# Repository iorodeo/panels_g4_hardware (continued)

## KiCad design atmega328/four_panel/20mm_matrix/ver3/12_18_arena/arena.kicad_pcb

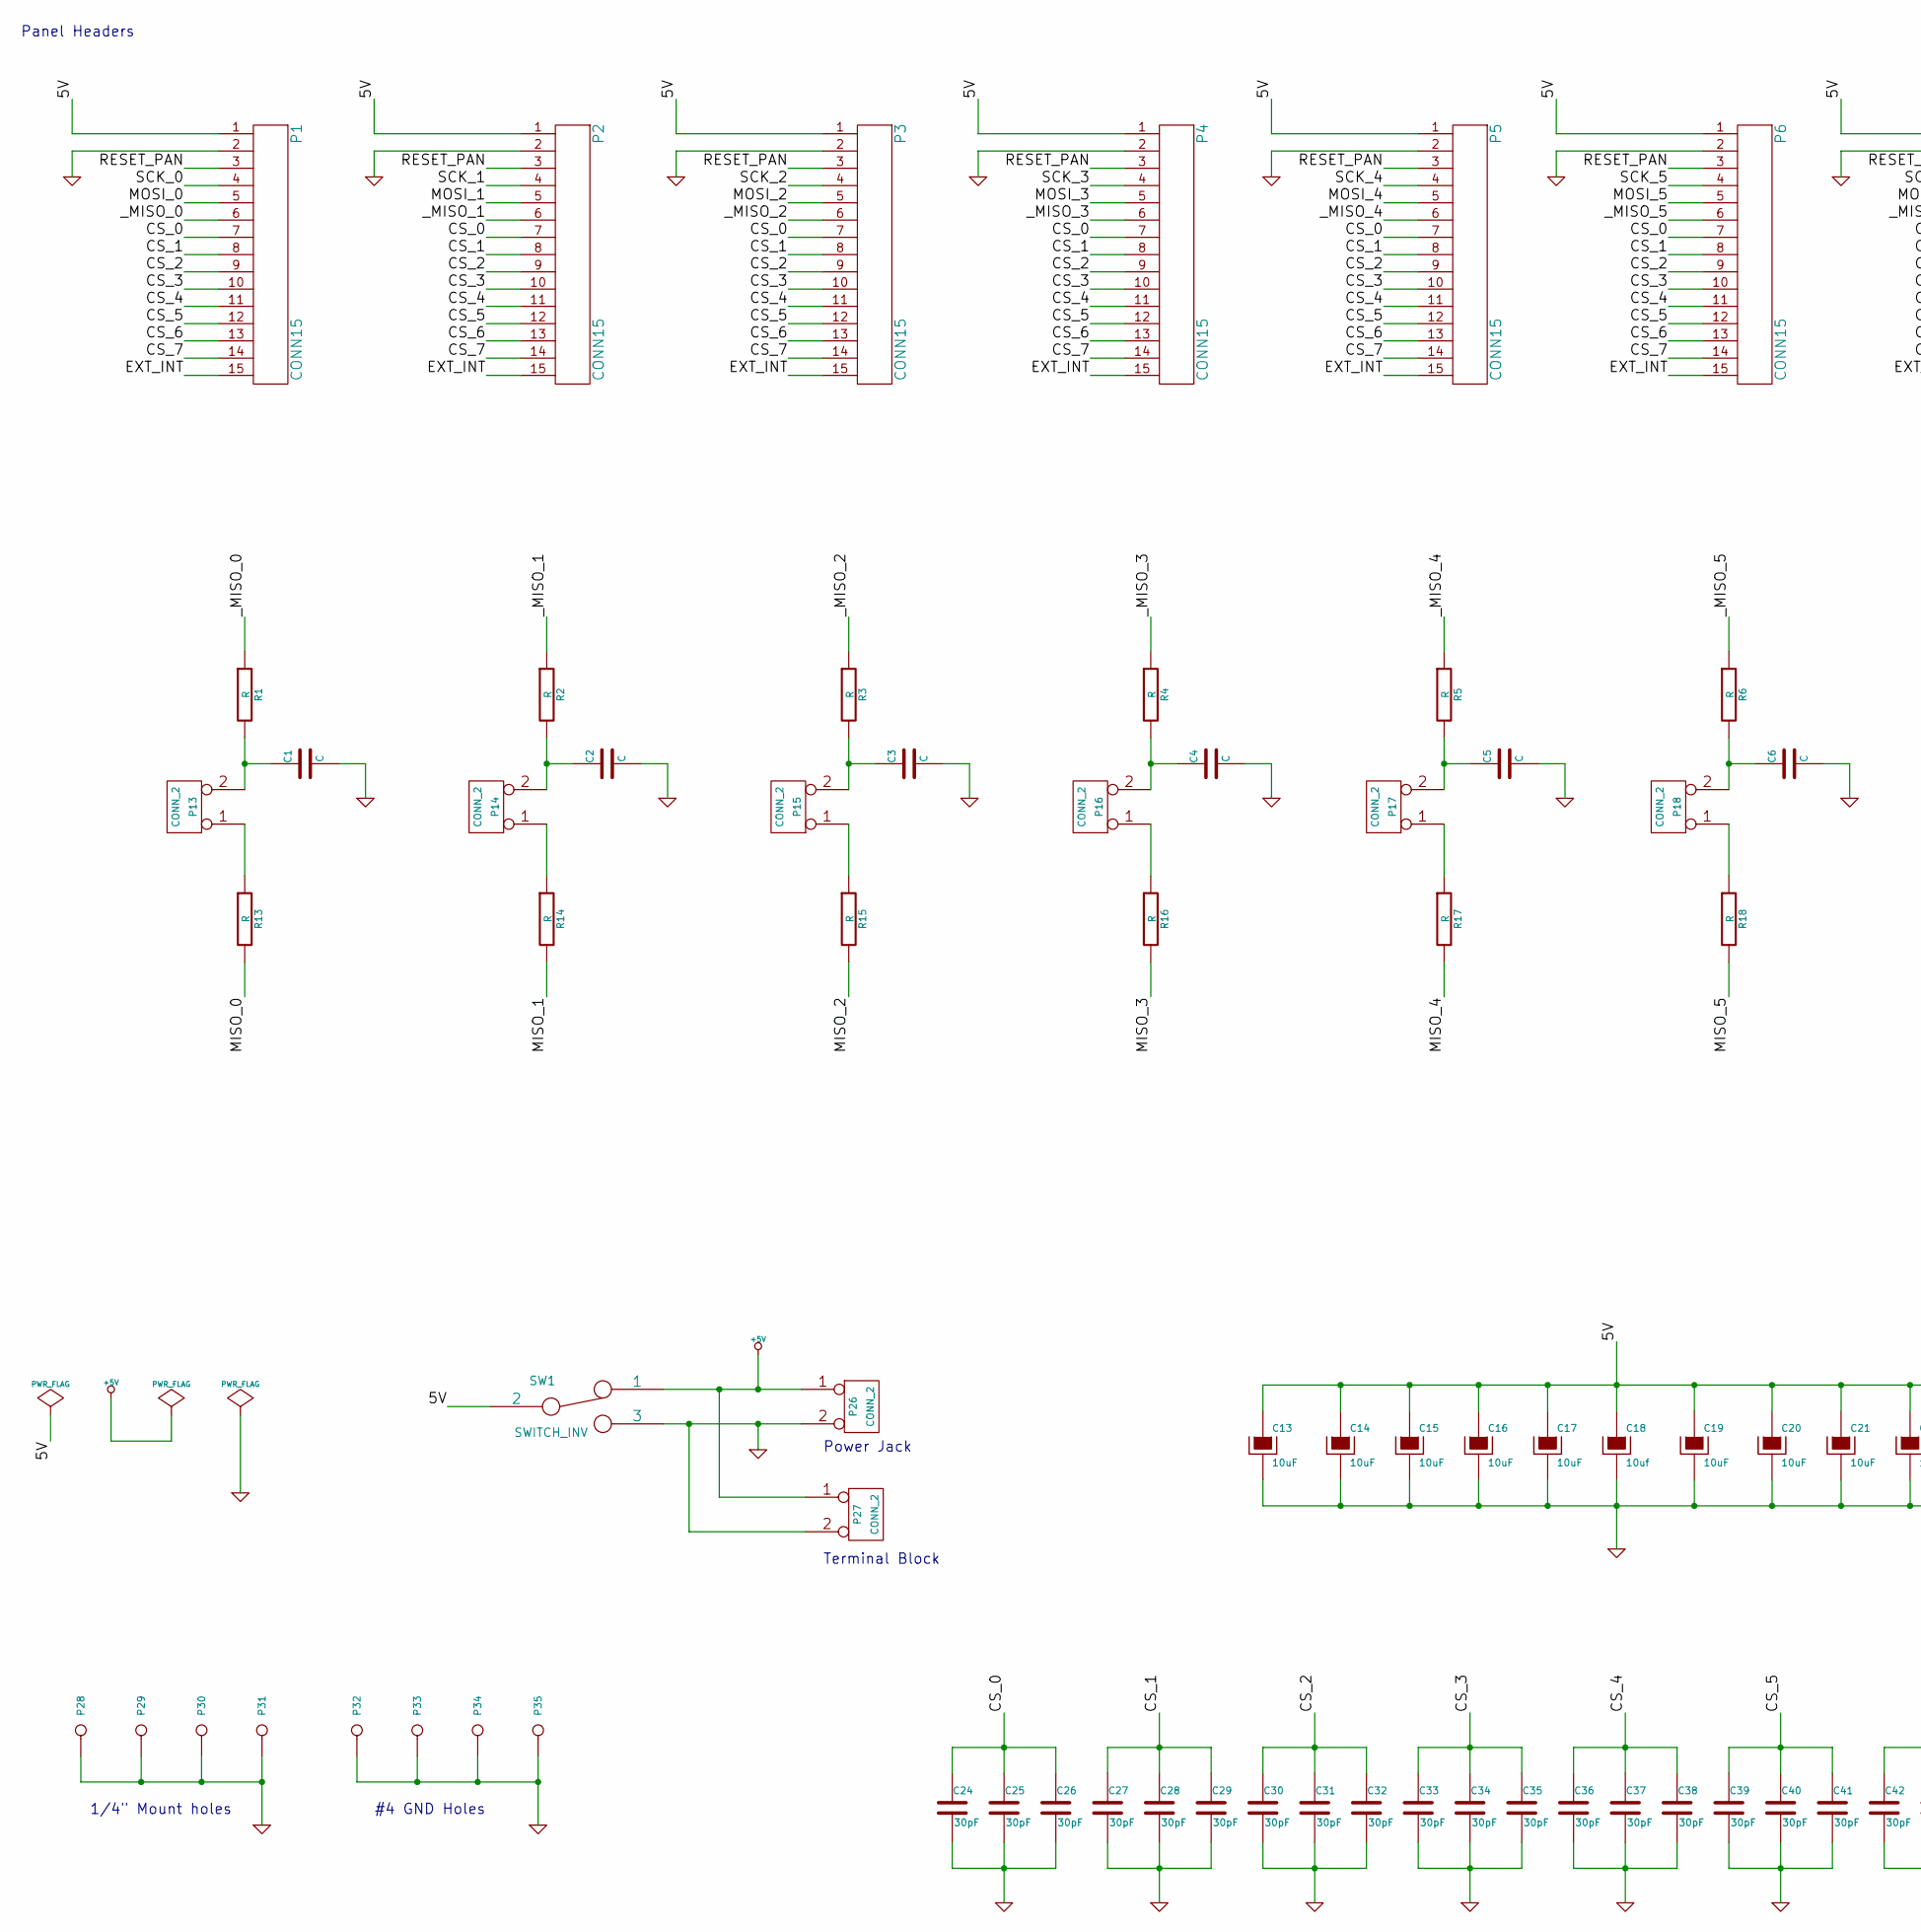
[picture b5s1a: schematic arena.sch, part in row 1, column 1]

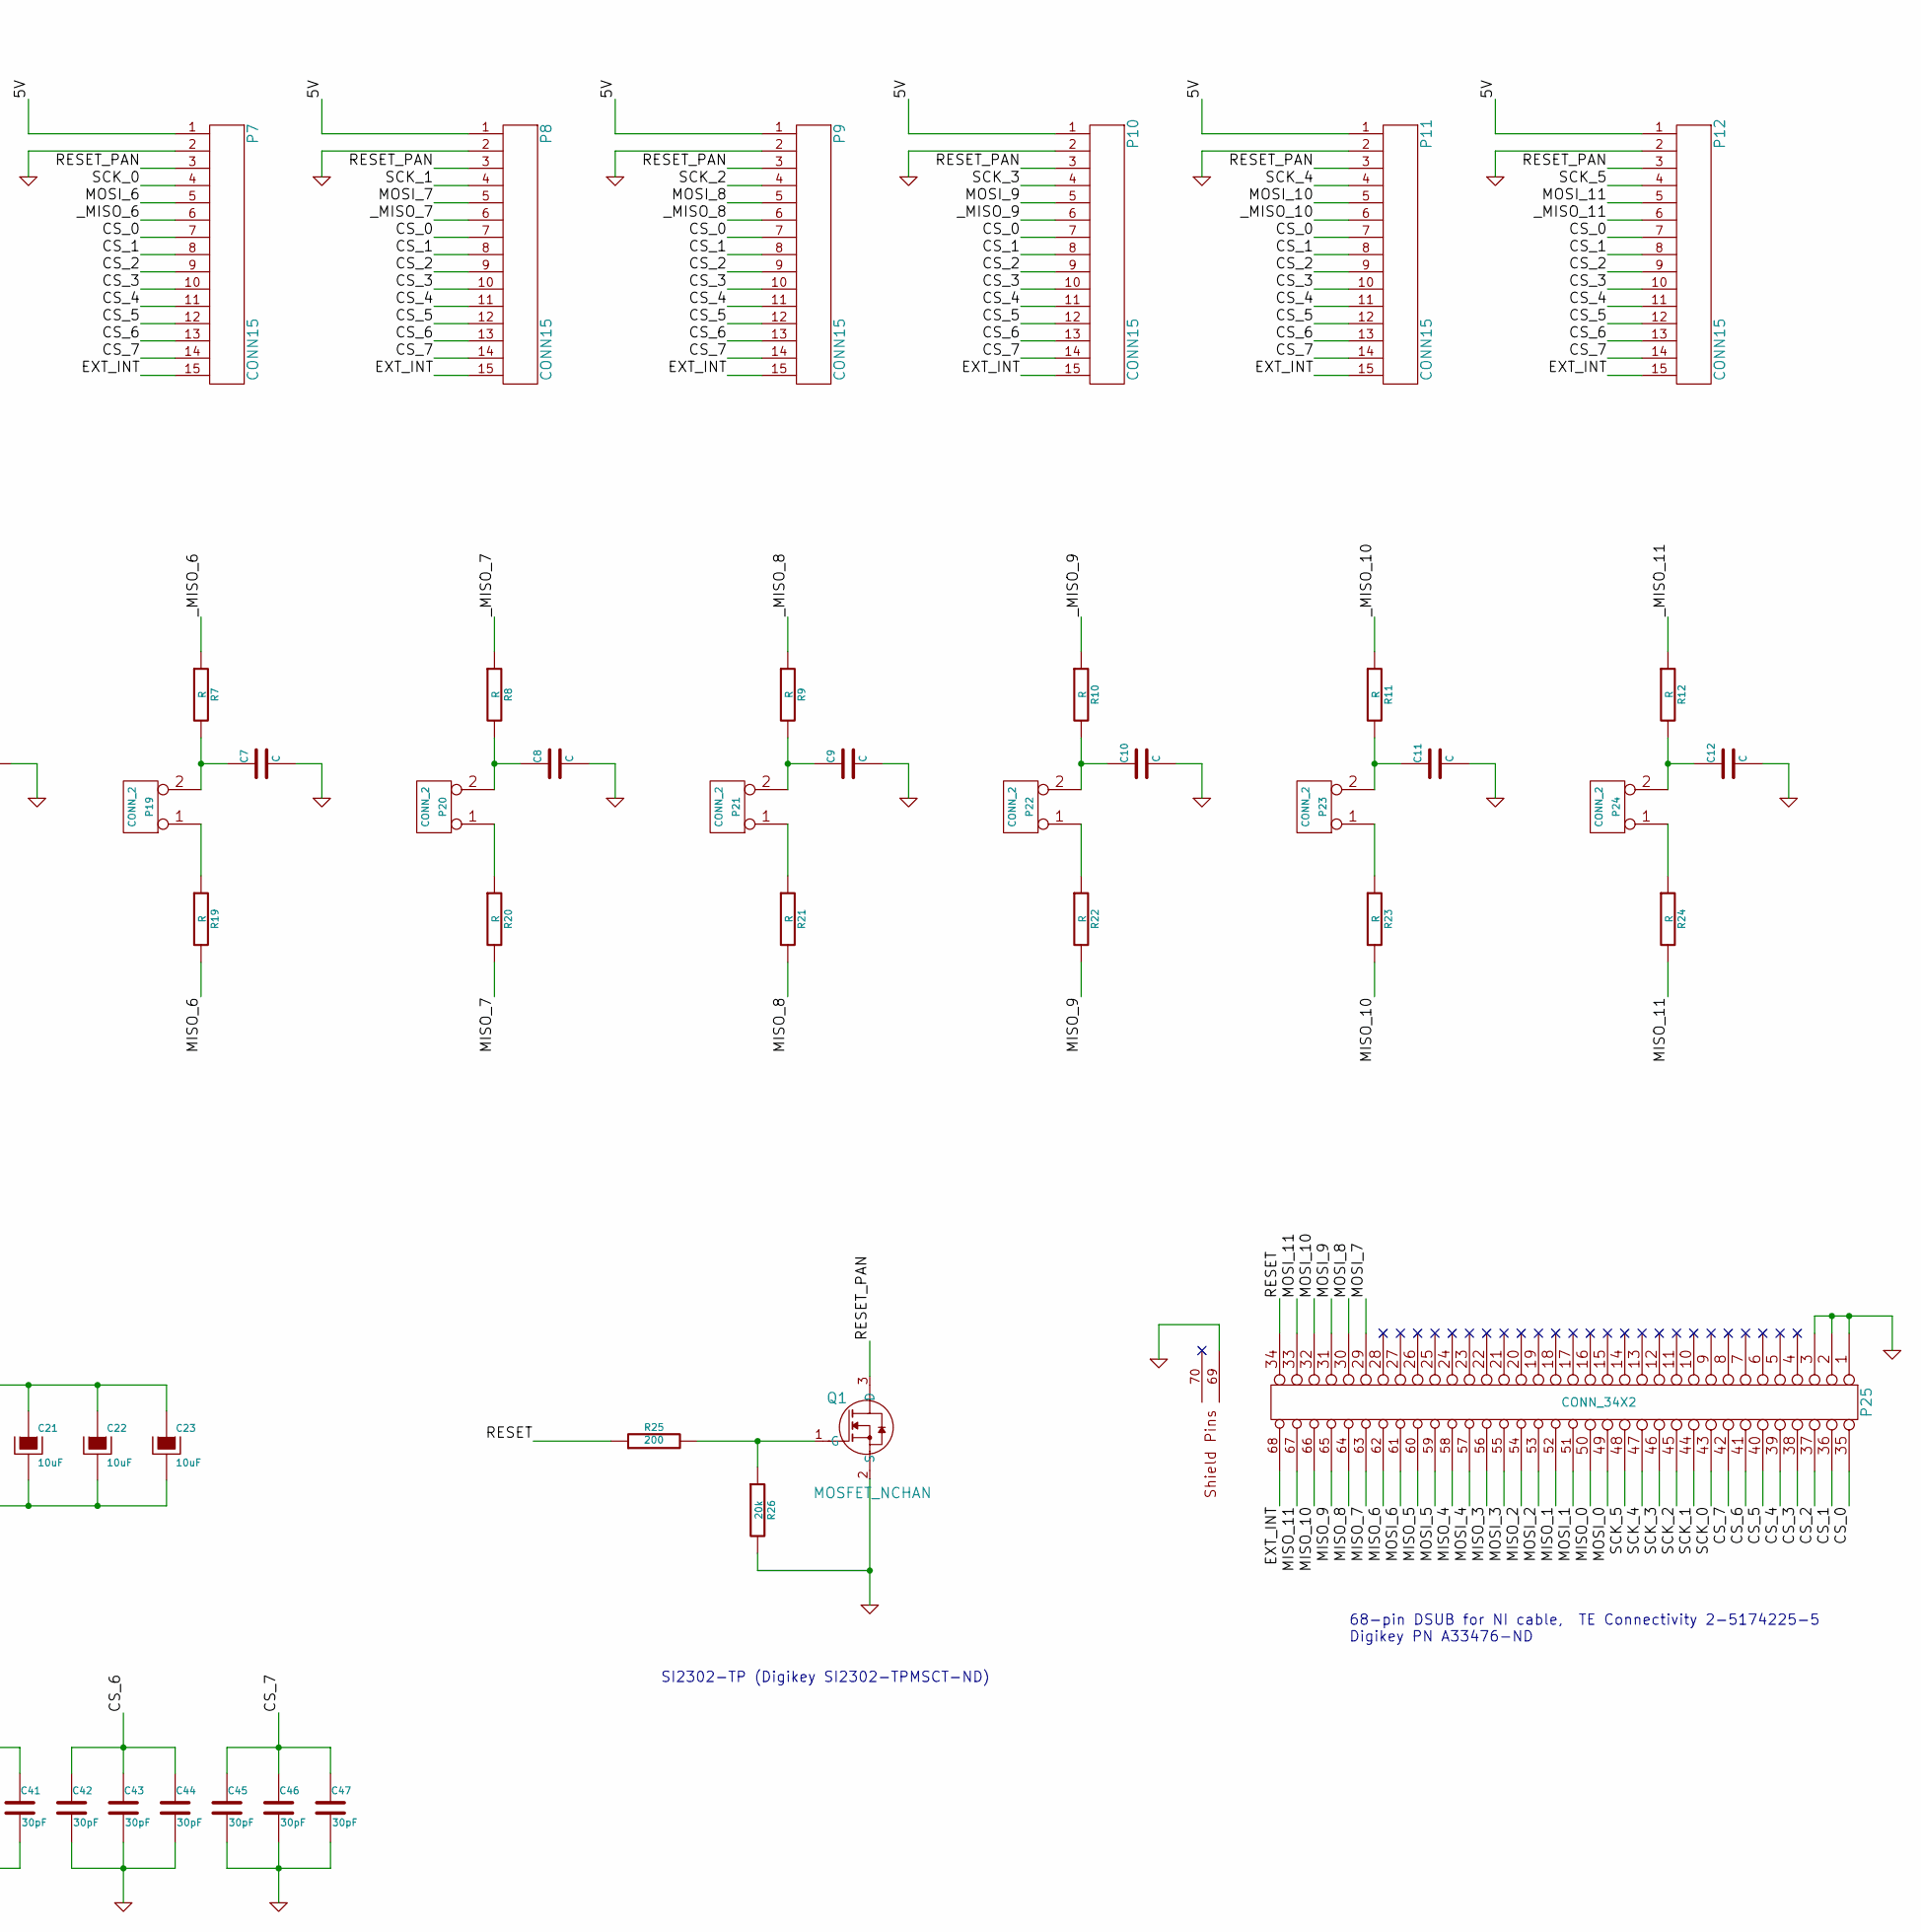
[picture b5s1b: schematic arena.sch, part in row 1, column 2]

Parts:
C1, C2, C3, C4, C5, C6, C7, C8, C9, C10, C11, C12: C
C13, C14, C15, C16, C17, C19, C20, C21, C22, C23: 10uF
C18: 10uf
C24, C25, C26, C27, C28, C29, C30, C31, C32, C33, C34, C35, C36, C37, C38, C39, C40, C41, C42, C43, C44, C45, C46, C47: 30pF
P1, P2, P3, P4, P5, P6, P7, P8, P9, P10, P11, P12: CONN15
P13, P14, P15, P16, P17, P18, P19, P20, P21, P22, P23, P24, P26, P27: CONN_2
P25: CONN_34X2
P28, P29, P30, P31, P32, P33, P34, P35: CONN_1
Q1: MOSFET_NCHAN
R1, R2, R3, R4, R5, R6, R7, R8, R9, R10, R11, R12, R13, R14, R15, R16, R17, R18, R19, R20, R21, R22, R23, R24: R
R25: 200
R26: 20k
SW1: SWITCH_INV

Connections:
+5V: P26.1, P27.1, SW1.1
/5V: C13.1, C14.1, C15.1, C16.1, C17.1, C18.1, C19.1, C20.1, C21.1, C22.1, C23.1, P1.1, P2.1, P3.1, P4.1, P5.1, P6.1, P7.1, P8.1, P9.1, P10.1, P11.1, P12.1, SW1.2
/CS_0: C24.1, C25.1, C26.1, P1.7, P2.7, P3.7, P4.7, P5.7, P6.7, P7.7, P8.7, P9.7, P10.7, P11.7, P12.7, P25.35
/CS_1: C27.1, C28.1, C29.1, P1.8, P2.8, P3.8, P4.8, P5.8, P6.8, P7.8, P8.8, P9.8, P10.8, P11.8, P12.8, P25.36
/CS_2: C30.1, C31.1, C32.1, P1.9, P2.9, P3.9, P4.9, P5.9, P6.9, P7.9, P8.9, P9.9, P10.9, P11.9, P12.9, P25.37
/CS_3: C33.1, C34.1, C35.1, P1.10, P2.10, P3.10, P4.10, P5.10, P6.10, P7.10, P8.10, P9.10, P10.10, P11.10, P12.10, P25.38
/CS_4: C36.1, C37.1, C38.1, P1.11, P2.11, P3.11, P4.11, P5.11, P6.11, P7.11, P8.11, P9.11, P10.11, P11.11, P12.11, P25.39
/CS_5: C39.1, C40.1, C41.1, P1.12, P2.12, P3.12, P4.12, P5.12, P6.12, P7.12, P8.12, P9.12, P10.12, P11.12, P12.12, P25.40
/CS_6: C42.1, C43.1, C44.1, P1.13, P2.13, P3.13, P4.13, P5.13, P6.13, P7.13, P8.13, P9.13, P10.13, P11.13, P12.13, P25.41
/CS_7: C45.1, C46.1, C47.1, P1.14, P2.14, P3.14, P4.14, P5.14, P6.14, P7.14, P8.14, P9.14, P10.14, P11.14, P12.14, P25.42
/EXT_INT: P1.15, P2.15, P3.15, P4.15, P5.15, P6.15, P7.15, P8.15, P9.15, P10.15, P11.15, P12.15, P25.68
/MISO_0: P25.50, R13.2
/MISO_1: P25.52, R14.2
/MISO_2: P25.54, R15.2
/MISO_3: P25.56, R16.2
/MISO_4: P25.58, R17.2
/MISO_5: P25.60, R18.2
/MISO_6: P25.62, R19.2
/MISO_7: P25.63, R20.2
/MISO_8: P25.64, R21.2
/MISO_9: P25.65, R22.2
/MISO_10: P25.66, R23.2
/MISO_11: P25.67, R24.2
/MOSI_0: P1.5, P25.49
/MOSI_1: P2.5, P25.51
/MOSI_2: P3.5, P25.53
/MOSI_3: P4.5, P25.55
/MOSI_4: P5.5, P25.57
/MOSI_5: P6.5, P25.59
/MOSI_6: P7.5, P25.61
/MOSI_7: P8.5, P25.29
/MOSI_8: P9.5, P25.30
/MOSI_9: P10.5, P25.31
/MOSI_10: P11.5, P25.32
/MOSI_11: P12.5, P25.33
/RESET: P25.34, R25.1
/RESET_PAN: P1.3, P2.3, P3.3, P4.3, P5.3, P6.3, P7.3, P8.3, P9.3, P10.3, P11.3, P12.3, Q1.3 (D)
/SCK_0: P1.4, P7.4, P25.43
/SCK_1: P2.4, P8.4, P25.44
/SCK_2: P3.4, P9.4, P25.45
/SCK_3: P4.4, P10.4, P25.46
/SCK_4: P5.4, P11.4, P25.47
/SCK_5: P6.4, P12.4, P25.48
/_MISO_0: P1.6, R1.1
/_MISO_1: P2.6, R2.1
/_MISO_2: P3.6, R3.1
/_MISO_3: P4.6, R4.1
/_MISO_4: P5.6, R5.1
/_MISO_5: P6.6, R6.1
/_MISO_6: P7.6, R7.1
/_MISO_7: P8.6, R8.1
/_MISO_8: P9.6, R9.1
/_MISO_9: P10.6, R10.1
/_MISO_10: P11.6, R11.1
/_MISO_11: P12.6, R12.1
GND: C1.2, C2.2, C3.2, C4.2, C5.2, C6.2, C7.2, C8.2, C9.2, C10.2, C11.2, C12.2, C13.2, C14.2, C15.2, C16.2, C17.2, C18.2, C19.2, C20.2, C21.2, C22.2, C23.2, C24.2, C25.2, C26.2, C27.2, C28.2, C29.2, C30.2, C31.2, C32.2, C33.2, C34.2, C35.2, C36.2, C37.2, C38.2, C39.2, C40.2, C41.2, C42.2, C43.2, C44.2, C45.2, C46.2, C47.2, P1.2, P2.2, P3.2, P4.2, P5.2, P6.2, P7.2, P8.2, P9.2, P10.2, P11.2, P12.2, P25.1, P25.2, P25.3, P25.69, P26.2 (PM), P27.2 (PM), P28.1, P29.1, P30.1, P31.1, P32.1, P33.1, P34.1, P35.1, Q1.2 (S), R26.2, SW1.3
unnamed: P24.1, R24.1
unnamed: P23.1, R23.1
unnamed: P20.1, R20.1
unnamed: P22.1, R22.1
unnamed: P21.1, R21.1
unnamed: P19.1, R19.1
unnamed: P18.1, R18.1
unnamed: P17.1, R17.1
unnamed: P16.1, R16.1
unnamed: P15.1, R15.1
unnamed: P14.1, R14.1
unnamed: P13.1, R13.1
unnamed: C4.1, P16.2 (PM), R4.2
unnamed: C3.1, P15.2 (PM), R3.2
unnamed: C2.1, P14.2 (PM), R2.2
unnamed: C1.1, P13.2 (PM), R1.2
unnamed: C5.1, P17.2 (PM), R5.2
unnamed: C12.1, P24.2 (PM), R12.2
unnamed: C7.1, P19.2 (PM), R7.2
unnamed: C6.1, P18.2 (PM), R6.2
unnamed: C9.1, P21.2 (PM), R9.2
unnamed: C8.1, P20.2 (PM), R8.2
unnamed: C11.1, P23.2 (PM), R11.2
unnamed: C10.1, P22.2 (PM), R10.2
unnamed: Q1.1 (G), R25.2, R26.1

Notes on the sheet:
Panel Headers
68-pin DSUB for NI cable, TE Connectivity 2-5174225-5 Digikey PN A33476-ND
SI2302-TP (Digikey SI2302-TPMSCT-ND)
1/4" Mount holes
Terminal Block
#4 GND Holes
Power Jack

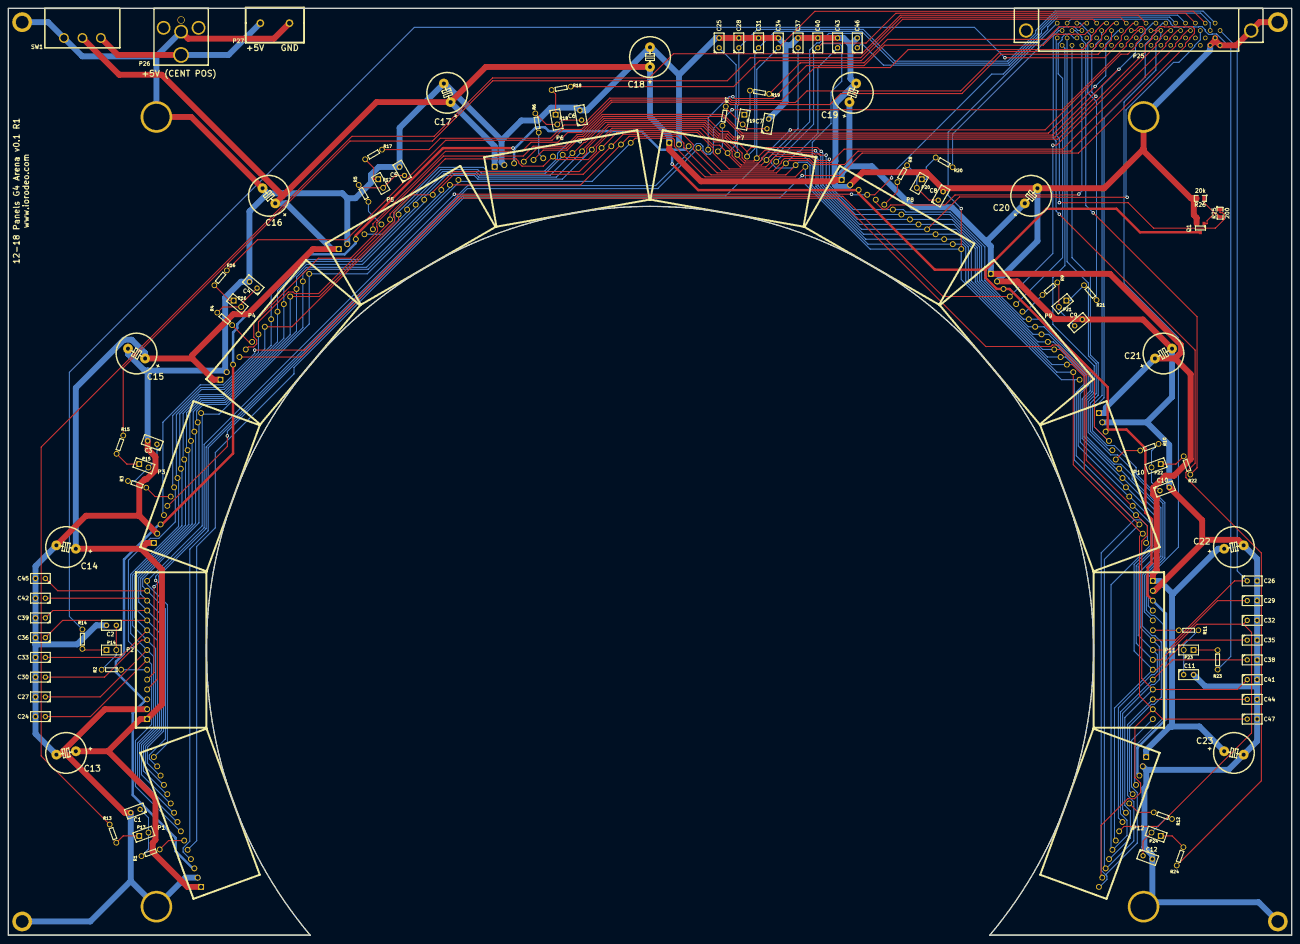
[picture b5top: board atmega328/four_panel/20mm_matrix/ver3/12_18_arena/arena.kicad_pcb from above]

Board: 2 copper layers, 330.2 x 238.5 mm, 110 parts (0 on the bottom side), 81 nets.
